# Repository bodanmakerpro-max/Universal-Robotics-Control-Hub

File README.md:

# Universal Robotics Control Hub

STM32-based robotics control PCB with two expansion connectors, two switched 12 V outputs, and regulated 5 V and 3.3 V power.

## Open the editable design

1. Click **Code > Download ZIP** on GitHub and extract it.
2. Open **KiCad/Unuversal robotic driver final versio.kicad_pro** in KiCad 10.
3. Open the schematic or PCB from KiCad Project Manager.

The `KiCad/` folder has the matching **.kicad_pro**, **.kicad_sch**, and **.kicad_pcb** files. All are editable. The original spelling is kept so the saved KiCad references are not changed.

## Folders

- **KiCad/** - current editable project (schematic, PCB, and settings).
- **Project Info/** - technical information, specifications, checks, and latest PCB screenshot.
- **Old Version/** - previous designs, pictures, reports, and other archived files. Not the current build.

See [Project Information](Project%20Info/PROJECT_INFO.md) for specs and known problems.

**Important:** The design has not been independently checked with KiCad ERC/DRC for this revision or tested on a physical board. Some 3D model files are missing. Do not order or power the board before checking the design.

Designed by Bodan Nikolov. Previous development and seminar work also involved Dusan.

No open-source license has been selected.

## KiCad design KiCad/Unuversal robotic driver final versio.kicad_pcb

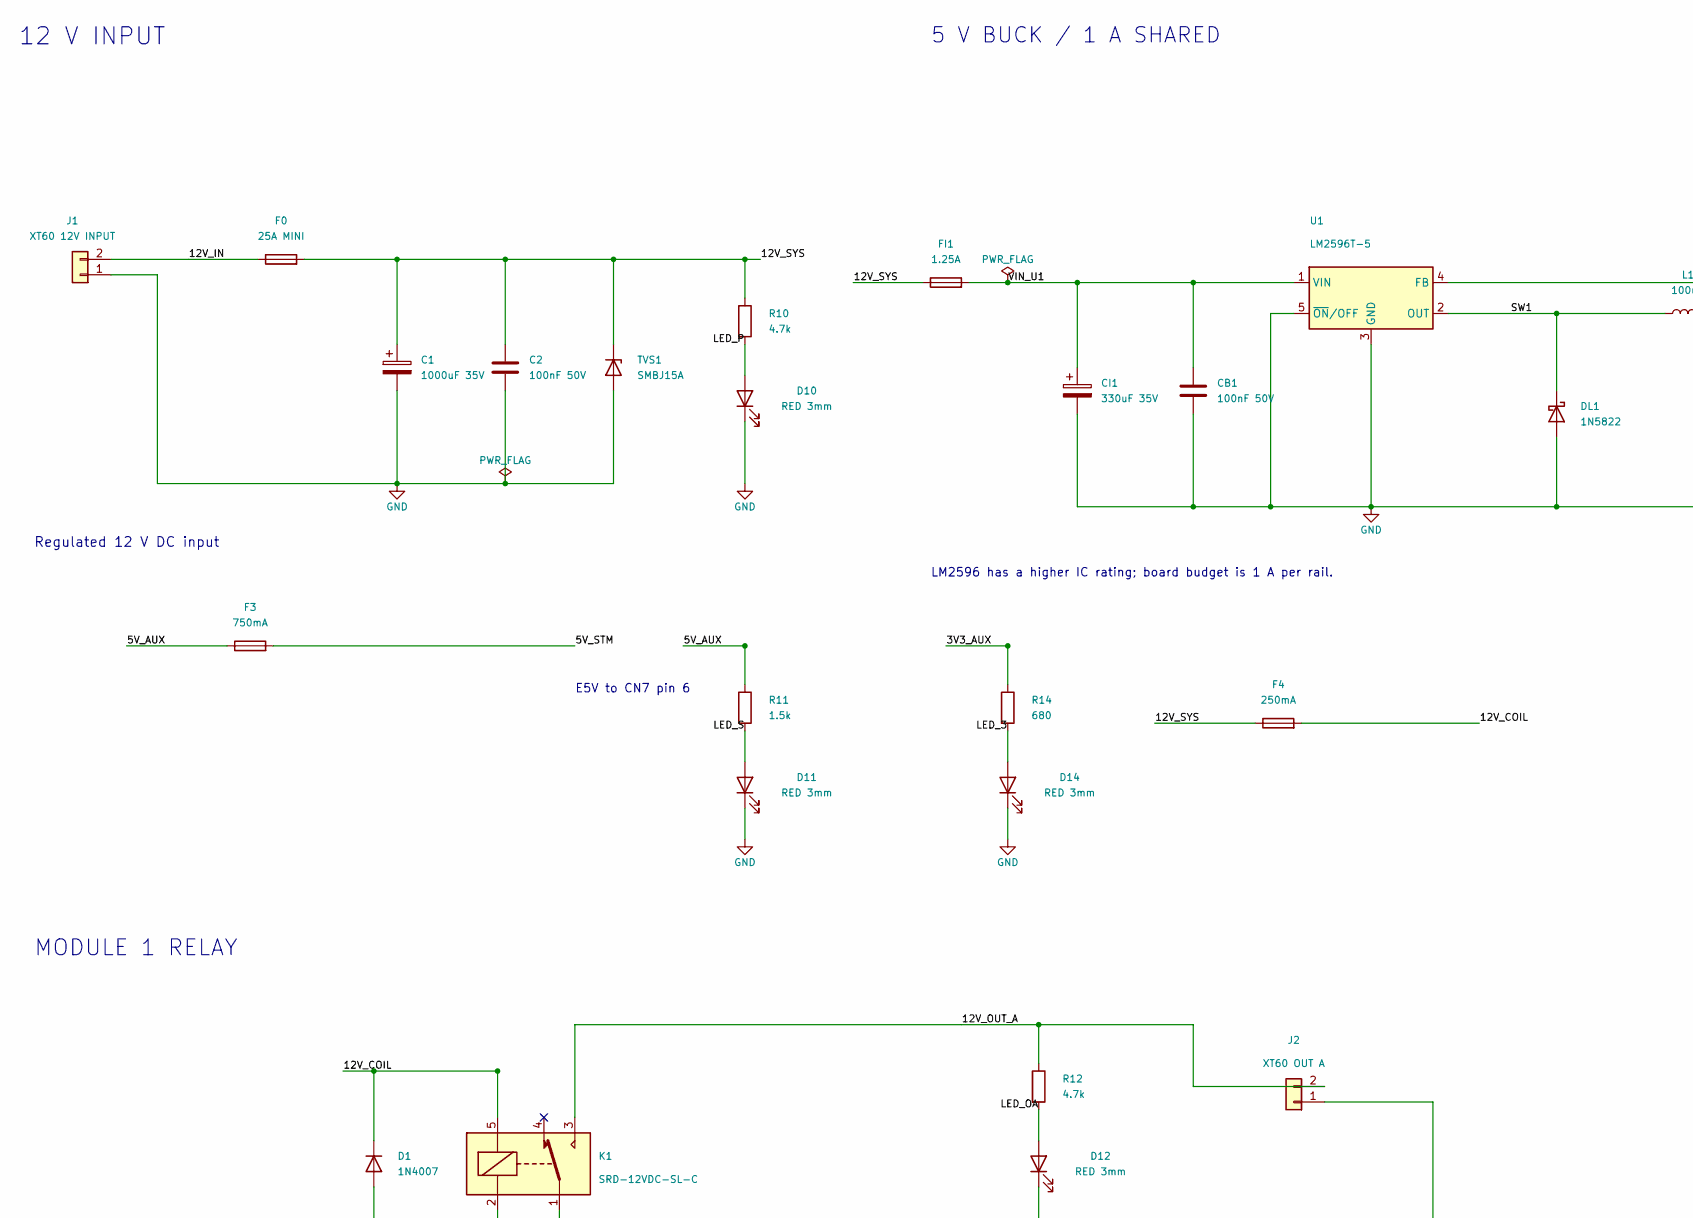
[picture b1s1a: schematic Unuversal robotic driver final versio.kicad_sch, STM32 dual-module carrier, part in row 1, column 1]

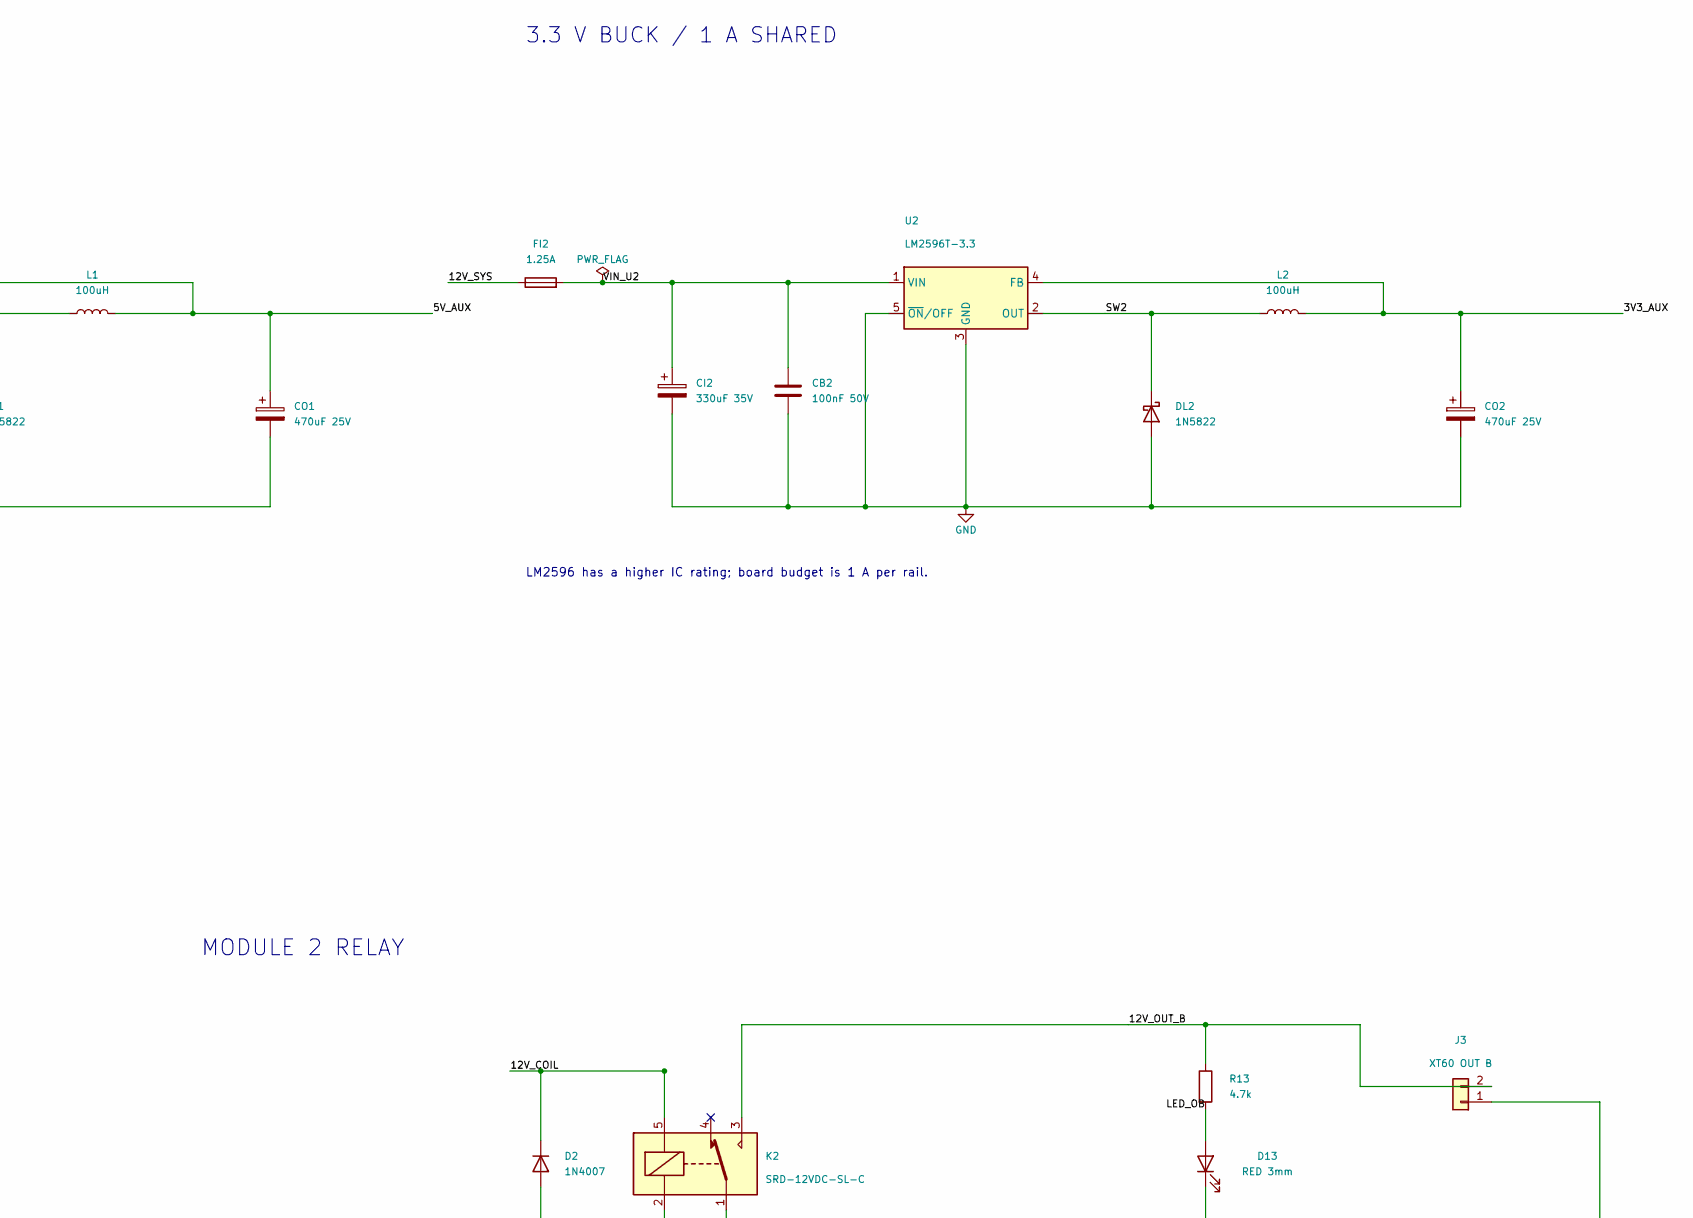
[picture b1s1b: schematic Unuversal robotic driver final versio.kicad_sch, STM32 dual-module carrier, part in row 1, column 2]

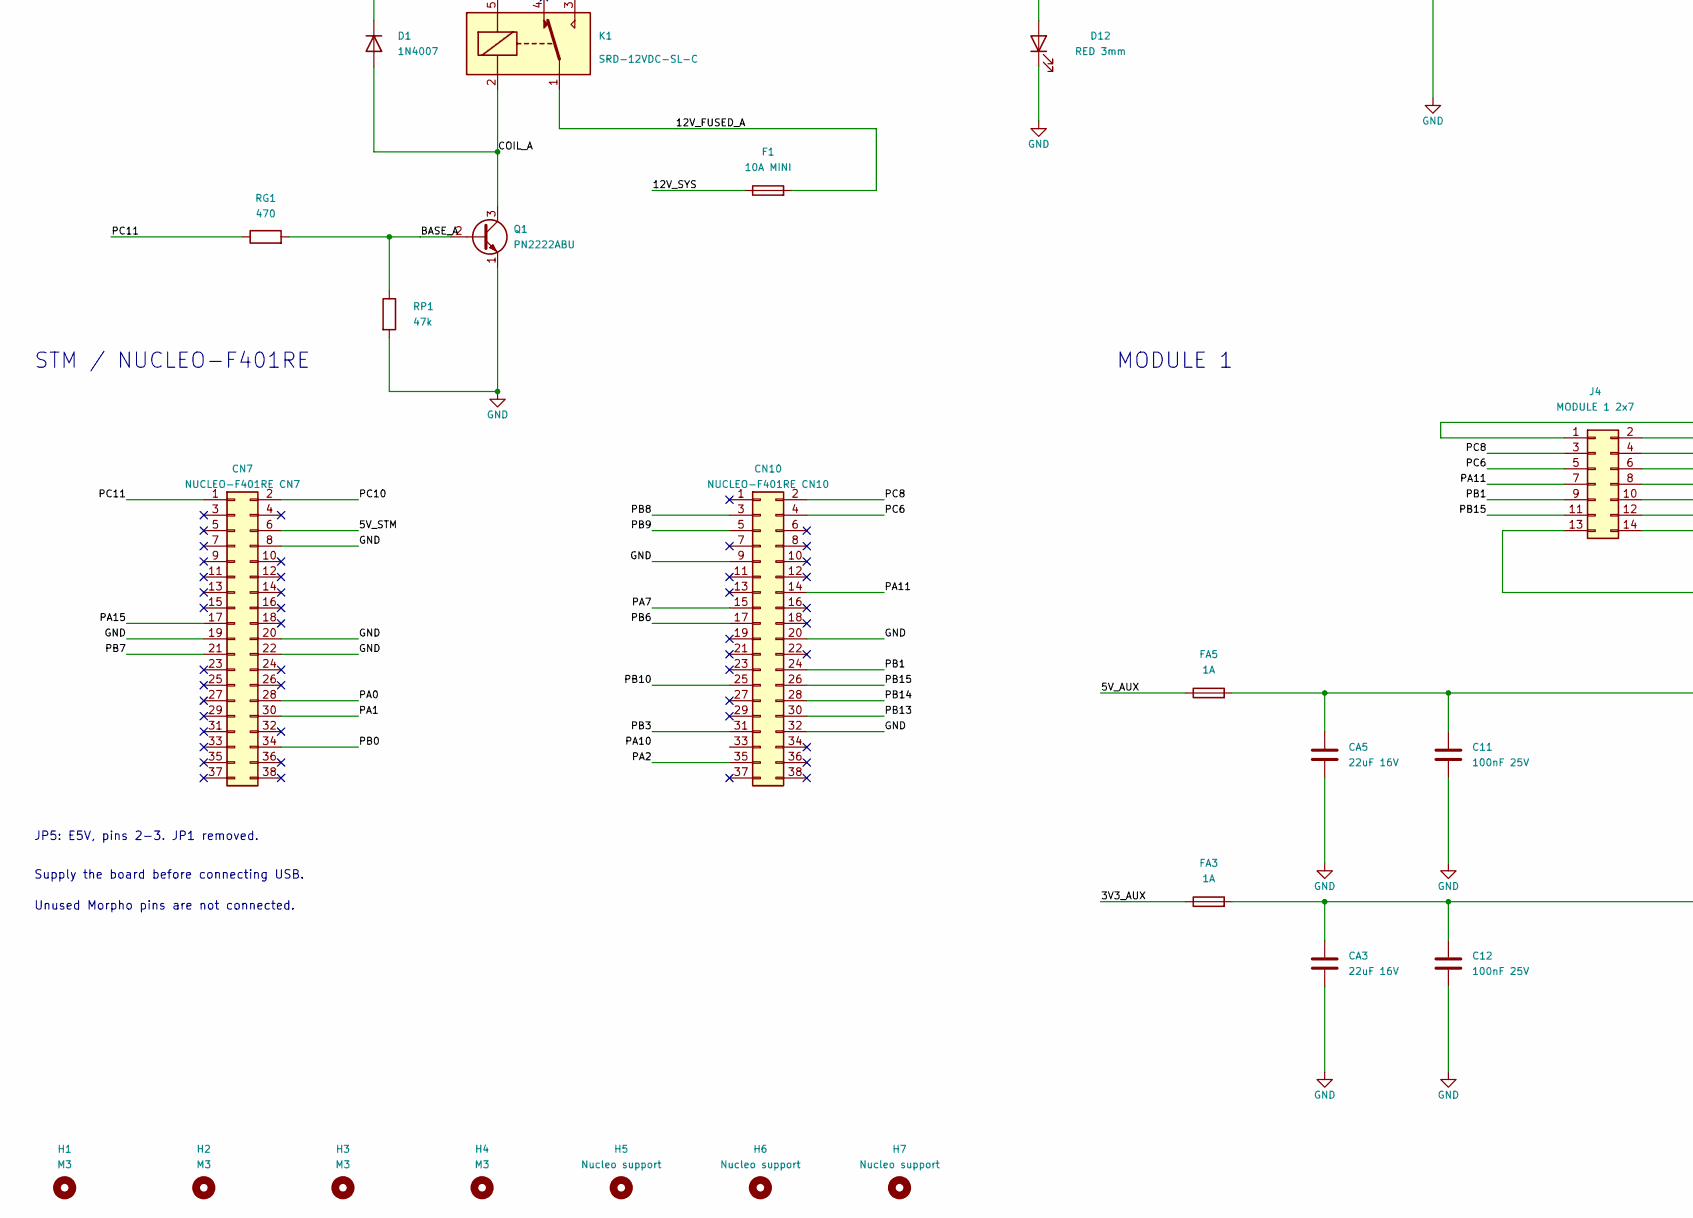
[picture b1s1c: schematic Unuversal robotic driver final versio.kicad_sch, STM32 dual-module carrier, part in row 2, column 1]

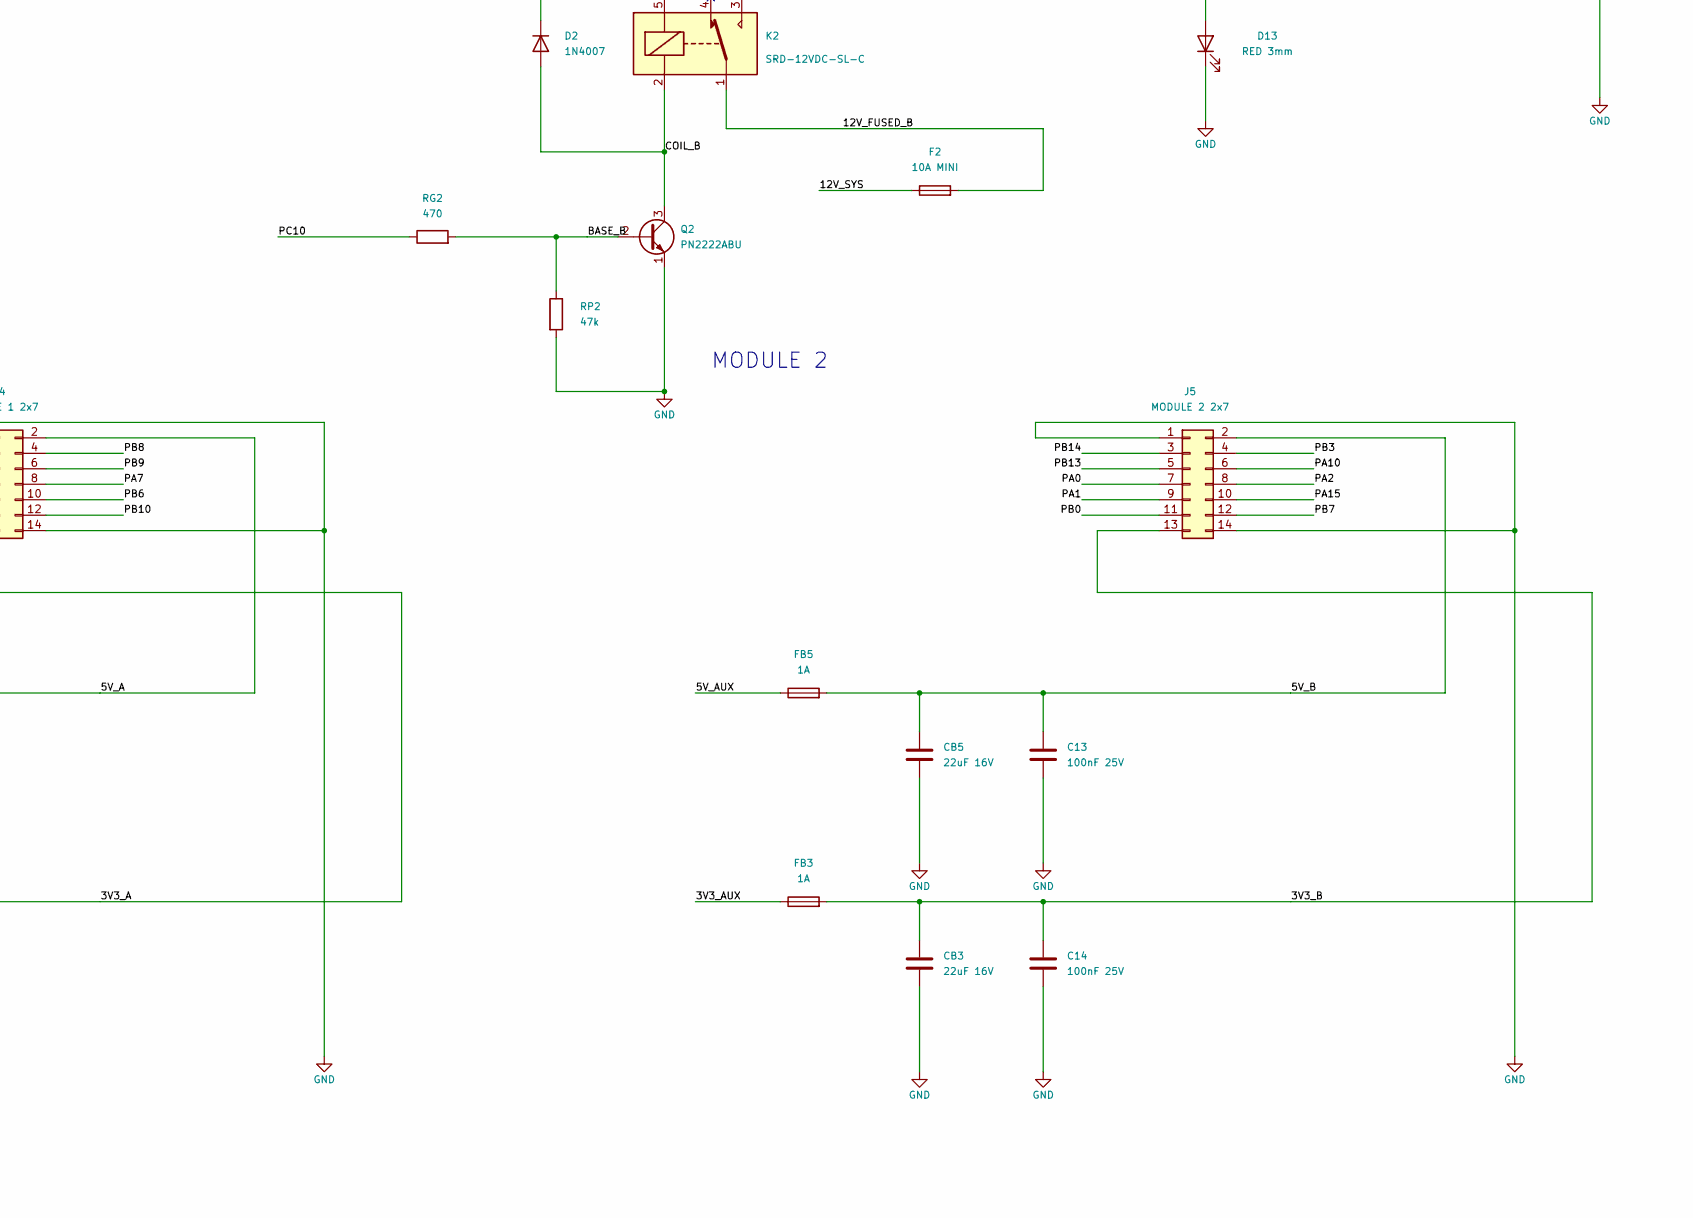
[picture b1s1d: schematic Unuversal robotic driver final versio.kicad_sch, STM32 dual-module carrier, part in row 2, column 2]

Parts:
C1: 1000uF 35V; CP_Radial_D12.5mm_P5.00mm
C2: 100nF 50V; C_1206_3216Metric_Pad1.33x1.80mm_HandSolder
C11, C12, C13, C14: 100nF 25V; C_1206_3216Metric_Pad1.33x1.80mm_HandSolder
CA3, CA5: 22uF 16V; C_1206_3216Metric_Pad1.33x1.80mm_HandSolder
CB1, CB2: 100nF 50V; C_1206_3216Metric_Pad1.33x1.80mm_HandSolder
CB3, CB5: 22uF 16V; C_1206_3216Metric_Pad1.33x1.80mm_HandSolder
CI1, CI2: 330uF 35V; CP_Radial_D10.0mm_P5.00mm
CN7: NUCLEO-F401RE CN7; Nucleo_Morpho_Socket_2x19
CN10: NUCLEO-F401RE CN10; Nucleo_Morpho_Socket_2x19
CO1, CO2: 470uF 25V; CP_Radial_D10.0mm_P5.00mm
D1, D2: 1N4007; D_DO-41_SOD81_P10.16mm_Horizontal
D10, D11, D12, D13, D14: RED 3mm; LED_D3.0mm
DL1, DL2: 1N5822; D_DO-201AD_P12.70mm_Horizontal
F0: 25A MINI; Fuseholder_Blade_Mini_Keystone_3568
F1, F2: 10A MINI; Fuseholder_Blade_Mini_Keystone_3568
F3: 750mA; Fuse_Littelfuse-NANO2-451_453
F4: 250mA; Fuse_Littelfuse-NANO2-451_453
FA3, FA5: 1A; Fuse_Littelfuse-NANO2-451_453
FB3, FB5: 1A; Fuse_Littelfuse-NANO2-451_453
FI1, FI2: 1.25A; Fuse_Littelfuse-NANO2-451_453
H1, H2, H3, H4: M3; MountingHole_3.2mm_M3
H5, H6, H7: Nucleo support; MountingHole_2.7mm_M2.5
J1: XT60 12V INPUT; AMASS_XT60-M_1x02_P7.20mm_Vertical
J2: XT60 OUT A; AMASS_XT60-F_1x02_P7.20mm_Vertical
J3: XT60 OUT B; AMASS_XT60-F_1x02_P7.20mm_Vertical
J4: MODULE 1 2x7; PinHeader_2x07_P2.54mm_Vertical
J5: MODULE 2 2x7; PinHeader_2x07_P2.54mm_Vertical
K1, K2: SRD-12VDC-SL-C; Relay_Songle_SRD_SPDT
L1, L2: 100uH; L_Bourns_SRR1260
Q1, Q2: PN2222ABU; TO-92_Inline_Wide
R10, R12, R13: 4.7k; R_Axial_DIN0207_L6.3mm_D2.5mm_P10.16mm_Horizontal
R11: 1.5k; R_Axial_DIN0207_L6.3mm_D2.5mm_P10.16mm_Horizontal
R14: 680; R_Axial_DIN0207_L6.3mm_D2.5mm_P10.16mm_Horizontal
RG1, RG2: 470; R_Axial_DIN0207_L6.3mm_D2.5mm_P10.16mm_Horizontal
RP1, RP2: 47k; R_Axial_DIN0207_L6.3mm_D2.5mm_P10.16mm_Horizontal
TVS1: SMBJ15A; D_SMB
U1: LM2596T-5; TO-220-5_Vertical_HandSolder
U2: LM2596T-3.3; TO-220-5_Vertical_HandSolder

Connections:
/3V3_A: C12.1, CA3.1, FA3.2, J4.13
/3V3_AUX: CO2.1, FA3.1, FB3.1, L2.2, R14.1, U2.4 (FB)
/3V3_B: C14.1, CB3.1, FB3.2, J5.13
/5V_A: C11.1, CA5.1, FA5.2, J4.2
/5V_AUX: CO1.1, F3.1, FA5.1, FB5.1, L1.2, R11.1, U1.4 (FB)
/5V_B: C13.1, CB5.1, FB5.2, J5.2
/5V_STM: CN7.6, F3.2
/12V_COIL: D1.1 (K), D2.1 (K), F4.2, K1.5, K2.5
/12V_FUSED_A: F1.2, K1.1
/12V_FUSED_B: F2.2, K2.1
/12V_IN: F0.1, J1.2
/12V_OUT_A: J2.2, K1.3, R12.1
/12V_OUT_B: J3.2, K2.3, R13.1
/12V_SYS: C1.1, C2.1, F0.2, F1.1, F2.1, F4.1, FI1.1, FI2.1, R10.1, TVS1.1 (K)
/BASE_A: Q1.2 (B), RG1.2, RP1.1
/BASE_B: Q2.2 (B), RG2.2, RP2.1
/COIL_A: D1.2 (A), K1.2, Q1.3 (C)
/COIL_B: D2.2 (A), K2.2, Q2.3 (C)
/LED_3: D14.2 (A), R14.2
/LED_OA: D12.2 (A), R12.2
/LED_OB: D13.2 (A), R13.2
/LED_P: D10.2 (A), R10.2
/LED_S: D11.2 (A), R11.2
/PA0: CN7.28, J5.7
/PA1: CN7.30, J5.9
/PA2: CN10.35, J5.8
/PA7: CN10.15, J4.8
/PA10: CN10.33, J5.6
/PA11: CN10.14, J4.7
/PA15: CN7.17, J5.10
/PB0: CN7.34, J5.11
/PB1: CN10.24, J4.9
/PB3: CN10.31, J5.4
/PB6: CN10.17, J4.10
/PB7: CN7.21, J5.12
/PB8: CN10.3, J4.4
/PB9: CN10.5, J4.6
/PB10: CN10.25, J4.12
/PB13: CN10.30, J5.5
/PB14: CN10.28, J5.3
/PB15: CN10.26, J4.11
/PC6: CN10.4, J4.5
/PC8: CN10.2, J4.3
/PC10: CN7.2, RG2.1
/PC11: CN7.1, RG1.1
/SW1: DL1.1 (K), L1.1, U1.2 (OUT)
/SW2: DL2.1 (K), L2.1, U2.2 (OUT)
/VIN_U1: CB1.1, CI1.1, FI1.2, U1.1 (VIN)
/VIN_U2: CB2.1, CI2.1, FI2.2, U2.1 (VIN)
GND: C1.2, C2.2, C11.2, C12.2, C13.2, C14.2, CA3.2, CA5.2, CB1.2, CB2.2, CB3.2, CB5.2, CI1.2, CI2.2, CN7.8, CN7.19, CN7.20, CN7.22, CN10.9, CN10.20, CN10.32, CO1.2, CO2.2, D10.1 (K), D11.1 (K), D12.1 (K), D13.1 (K), D14.1 (K), DL1.2 (A), DL2.2 (A), J1.1, J2.1, J3.1, J4.1, J4.14, J5.1, J5.14, Q1.1 (E), Q2.1 (E), RP1.2, RP2.2, TVS1.2 (A), U1.3 (GND), U1.5 (~ON/OFF), U2.3 (GND), U2.5 (~ON/OFF)

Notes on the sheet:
12 V INPUT
Regulated 12 V DC input
5 V BUCK / 1 A SHARED
LM2596 has a higher IC rating; board budget is 1 A per rail.
3.3 V BUCK / 1 A SHARED
E5V to CN7 pin 6
MODULE 1 RELAY
MODULE 2 RELAY
STM / NUCLEO-F401RE
JP5: E5V, pins 2-3. JP1 removed.
Supply the board before connecting USB.
Unused Morpho pins are not connected.
MODULE 1
MODULE 2

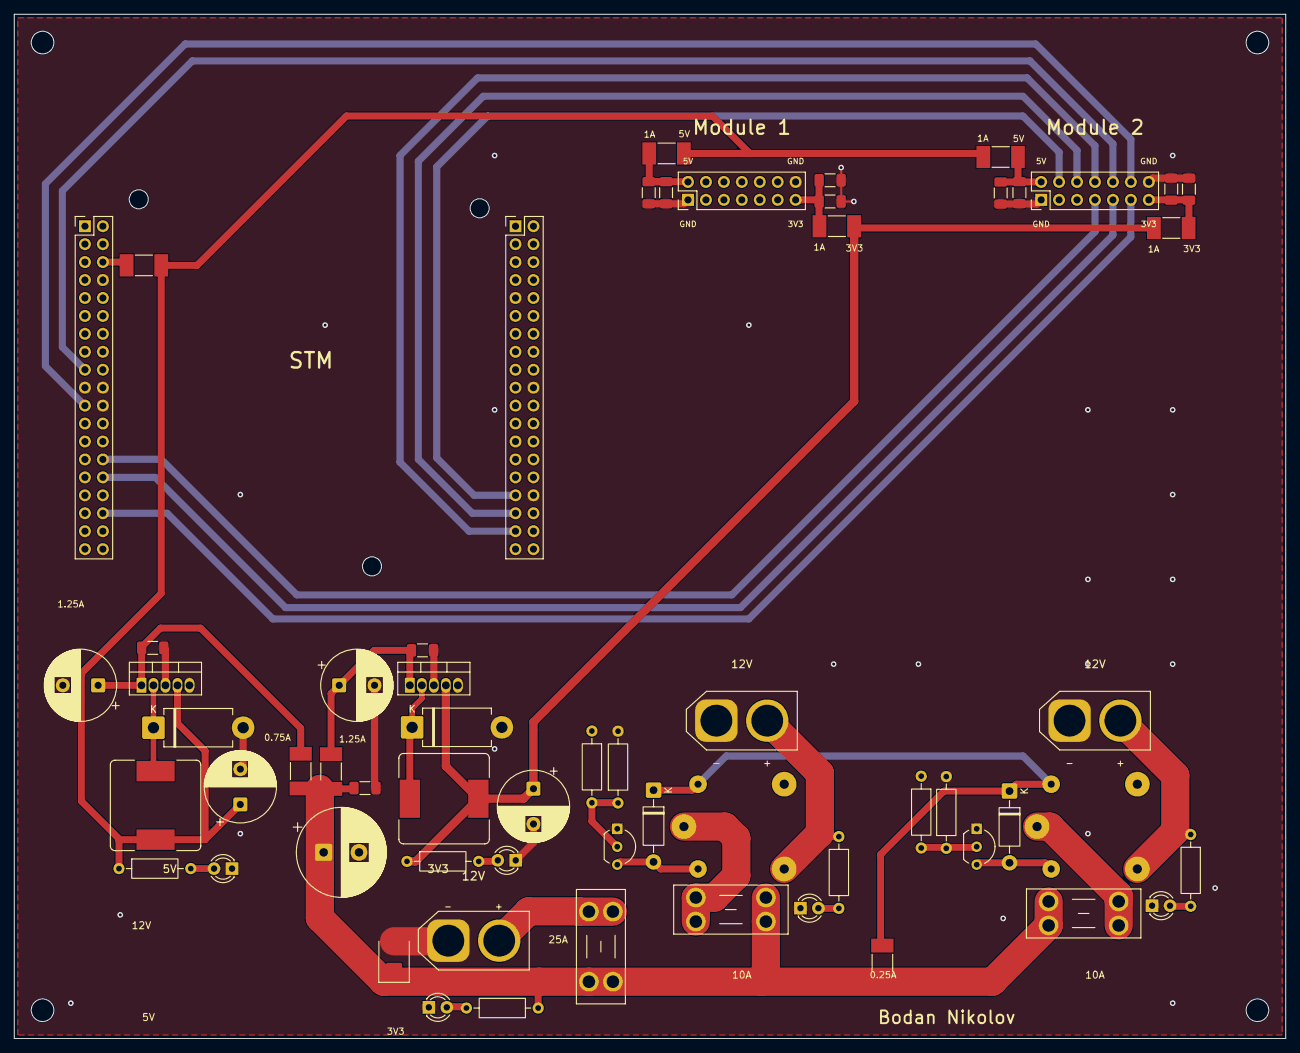
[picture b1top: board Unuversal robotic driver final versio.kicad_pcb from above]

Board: 4 copper layers, 180.0 x 145.0 mm, 68 parts (0 on the bottom side), 50 nets.
